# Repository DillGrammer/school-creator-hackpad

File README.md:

# Hackpad PCB — revision 1.0

Open **Hackpad.kicad_pro** in KiCad 10. The project includes its own symbol and footprint libraries; no care-package installation is needed. Original Desktop files were left unchanged.

CAD visualization, not a photograph of an assembled device.

This project was substantially generated and revised with ChatGPT/Codex assistance, following the owner's feature/layout choices and design review. See Software/Feature-status.md for unfinished integrations and Submission-status.md for funding status.

## What is finished

- 86.5 × 88.5 mm, two copper layers, 1.6 mm PCB.
- Six soldered MX switches in the established 3 × 2 layout.
- Clickable EC11 at top-left; 0.91-inch OLED immediately to its right.
- Seeed Studio XIAO RP2040 at top-right, USB-C facing the top edge.
- Routed signals, front/back ground pours, four 3.2 mm mounting holes.
- ERC, DRC and schematic parity reports included. All report zero issues.
- Gerber copper, masks, silkscreens, outline, and separate plated/non-plated drill files included.

The matching case is supplied in **Case/** as STEP and STL files, with an assembly guide and geometry checks. The native Fusion `Case/Hackpad_Case.f3d` includes editable base/cover features and a positioned knob. Case revision 1.1 corrects the CAD Y direction and knob placement; use the new case files, not earlier archives. Actual firmware and desktop-helper source are included in **Software/**; this is a development build, not a hardware-tested release. See **Software/Feature-status.md** for the exact remaining integration work.

## Pin map

View from above, USB-C at the top. Key numbers describe physical positions; existing SW references are preserved.

| Control | Reference / pad | XIAO label | RP2040 GPIO | Net |
|---|---|---|---|---|
| Top-left key | SW1 / 1 | D0 | 26 | KEY1 |
| Top-middle key | SW4 / 1 | D2 | 28 | KEY2 |
| Top-right key | SW2 / 1 | D6 | 0 | KEY3 |
| Bottom-left key | SW5 / 1 | D1 | 27 | KEY4 |
| Bottom-middle key | SW7 / 1 | D3 | 29 | KEY5 |
| Bottom-right key | SW3 / 1 | D7 | 1 | KEY6 |
| Encoder rotation A | SW6 / A | D10 | 3 | ENC_A |
| Encoder rotation B | SW6 / B | D9 | 4 | ENC_B |
| Encoder press / Enter | SW6 / S1 | D8 | 2 | ENC_CLICK |
| OLED data | J1 / 4 | D4 / SDA | 6 | OLED_SDA |
| OLED clock | J1 / 3 | D5 / SCL | 7 | OLED_SCL |
| OLED power | J1 / 2 | 3V3 | — | +3V3 |
| OLED ground | J1 / 1 | GND | — | GND |

All key pad 2 connections, encoder C, and encoder S2 connect to ground. Enable input pull-ups and software debounce for keys and encoder press. Use a quadrature decoder for rotation; configure its transitions-per-detent for the supplied encoder so one detent produces one menu step. Reverse direction in firmware if needed. Encoder press is independently wired and can mean Enter/select or another action by mode.

Six keys + three encoder inputs + two OLED signals use all 11 exposed GPIOs. Independent key wiring supports simultaneous presses without a switch matrix or diodes. Extra kit LEDs are not fitted in this design.

## Parts used from the published kit

| Quantity | Part |
|---:|---|
| 1 | Standard Seeed Studio XIAO RP2040, not RP2040 Plus |
| 6 | MX-style through-hole switches |
| 6 | 1u DSA keycaps |
| 1 | EC11 clickable rotary encoder |
| 1 | 0.91-inch 128 × 32 I²C OLED, GND–VCC–SCL–SDA |
| 1 | 4-pin 2.54 mm header supplied with/for OLED |
| 4 | M3 × 16 mm case screws, for planned enclosure |
| 4 | M3 heat-set inserts, for planned enclosure |

## Assembly assumptions

- The supplied encoder matches the Hackpad-style EC11 footprint: A/C/B terminals at 2.5 mm pitch, click terminals opposite, and two slotted metal anchors. Nominal shaft height is 20 mm. A knob is not listed in the published kit; a printable knob can be matched to the supplied shaft during case completion.
- OLED is mounted display-up and extends rightward from J1. **J1 pins run top-to-bottom: GND, 3V3, SCL, SDA.** The module envelope is assumed to be 38 × 12 mm; it is shown in the project footprint and drawing layer. Confirm the actual supplied module uses that header orientation before soldering.
- OLED is powered from 3.3 V. The common module includes I²C pull-ups; confirm that the supplied module has pull-ups to 3.3 V. Do not connect I²C pull-ups to 5 V. The MCU's weak internal pull-ups alone are not the design basis for a reliable I²C bus.
- XIAO uses the existing care-package hybrid footprint, with corrected RP2040 schematic pin names. Direct solder mounting is assumed for the planned case; tall sockets change the case fit.
- USB supplies the XIAO directly. Its 5 V breakout is deliberately unused. The circuit has no battery input.
- Switches are soldered, not hot-swap. The upper row was aligned to a common centre line; the original column spacing and lower row were preserved.
- EC11 switch anchor pads are mechanical only. They do not substitute for the C/S2 ground connections.

## Mechanical coordinates

Millimetres from PCB top-left; X right, Y down.

| Item | X | Y |
|---|---:|---:|
| Key column centres | 15.50 / 43.25 / 71.00 | — |
| Key row centres | — | 43.50 / 76.00 |
| Encoder shaft centre | 15.75 | 16.00 |
| OLED GND header pin | 27.50 | 12.19 |
| XIAO footprint centre | 75.50 | 10.50 |
| Mount H1 | 4.50 | 4.50 |
| Mount H2 | 82.00 | 29.50 |
| Mount H3 | 4.50 | 84.00 |
| Mount H4 | 82.00 | 84.00 |

The matching case uses a rounded base and removable stepped cover, four M3 screws and heat-set inserts. See **Case/Assembly-guide.md** for the assembly order, printing orientation and component fit assumptions.

## Manufacturing files

Use the Gerbers ZIP, including both drill files, for the PCB only. Board specification: two layers, FR-4, 1.6 mm thickness; design uses 0.25 mm traces, 0.20 mm minimum clearance, 0.60/0.30 mm vias, and 0.50 mm minimum copper-to-edge clearance. The Stardance design project has been created; no funding application or manufacturing order has been submitted. See Submission-status.md.

The checks validate the CAD files; this design has not been physically assembled or tested. The case has CAD checks but no physical print test; software has automated logic/display tests but still requires hardware and app integration testing.

## Sources

- [Hackpad / Stardance](https://hackpad.hackclub.com/)
- [Hack Club published kit contents](https://blueprint.hackclub.com/hackpad/parts)
- [Hackpad component guidance](https://hackpad.hackclub.com/add-components)
- [Seeed XIAO RP2040 pin map](https://wiki.seeedstudio.com/XIAO-RP2040/)

Footprints are derived from KiCad's installed libraries and the user's existing Hackpad care package. The XIAO's fabrication graphics were retained, and its courtyard added. The OLED header footprint was expanded to describe the full module envelope.

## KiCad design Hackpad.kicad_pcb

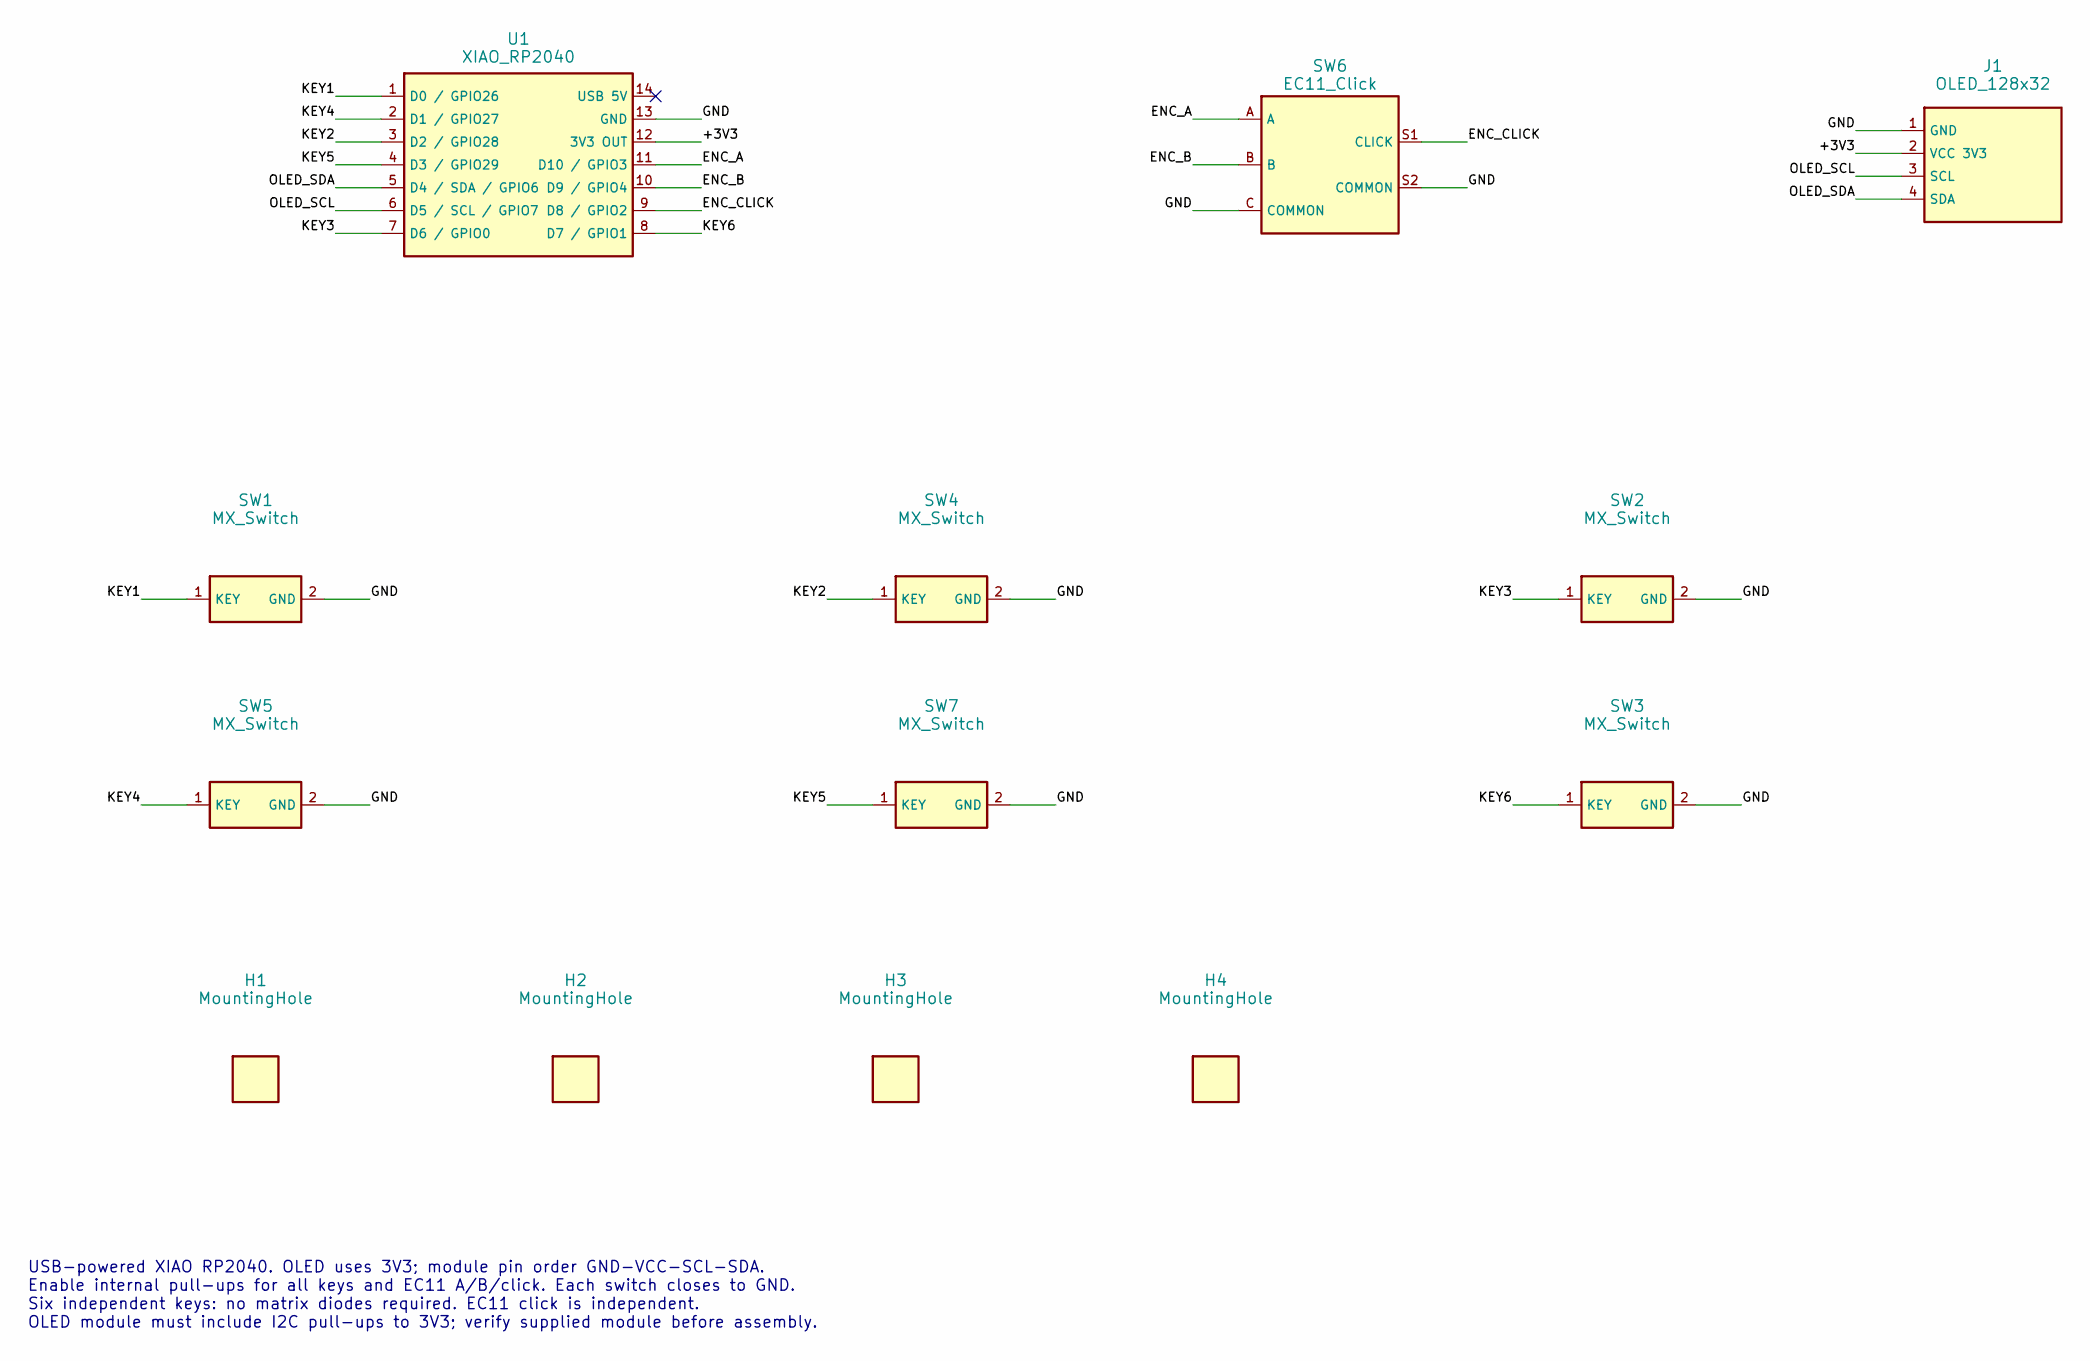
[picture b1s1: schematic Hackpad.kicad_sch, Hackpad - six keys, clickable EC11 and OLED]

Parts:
H1, H2, H3, H4: MountingHole; MountingHole_3.2mm_M3
J1: OLED_128x32; OLED_091_GND_VCC_SCL_SDA
SW1, SW2, SW3, SW4, SW5, SW7: MX_Switch; SW_Cherry_MX_1.00u_PCB
SW6: EC11_Click; RotaryEncoder_Alps_EC11E-Switch_Vertical_H20mm
U1: XIAO_RP2040; XIAO-Generic-Hybrid-14P-2.54-21X17.8MM

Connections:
/+3V3: J1.2 (VCC 3V3), U1.12 (3V3 OUT)
/ENC_A: SW6.A, U1.11 (D10 / GPIO3)
/ENC_B: SW6.B, U1.10 (D9 / GPIO4)
/ENC_CLICK: SW6.S1 (CLICK), U1.9 (D8 / GPIO2)
/GND: J1.1 (GND), SW1.2 (GND), SW2.2 (GND), SW3.2 (GND), SW4.2 (GND), SW5.2 (GND), SW6.C (COMMON), SW6.S2 (COMMON), SW7.2 (GND), U1.13 (GND)
/KEY1: SW1.1 (KEY), U1.1 (D0 / GPIO26)
/KEY2: SW4.1 (KEY), U1.3 (D2 / GPIO28)
/KEY3: SW2.1 (KEY), U1.7 (D6 / GPIO0)
/KEY4: SW5.1 (KEY), U1.2 (D1 / GPIO27)
/KEY5: SW7.1 (KEY), U1.4 (D3 / GPIO29)
/KEY6: SW3.1 (KEY), U1.8 (D7 / GPIO1)
/OLED_SCL: J1.3 (SCL), U1.6 (D5 / SCL / GPIO7)
/OLED_SDA: J1.4 (SDA), U1.5 (D4 / SDA / GPIO6)

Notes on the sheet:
USB-powered XIAO RP2040. OLED uses 3V3; module pin order GND-VCC-SCL-SDA. Enable internal pull-ups for all keys and EC11 A/B/click. Each switch closes to GND. Six independent keys: no matrix diodes required. EC11 click is independent. OLED module must include I2C pull-ups to 3V3; verify supplied mo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

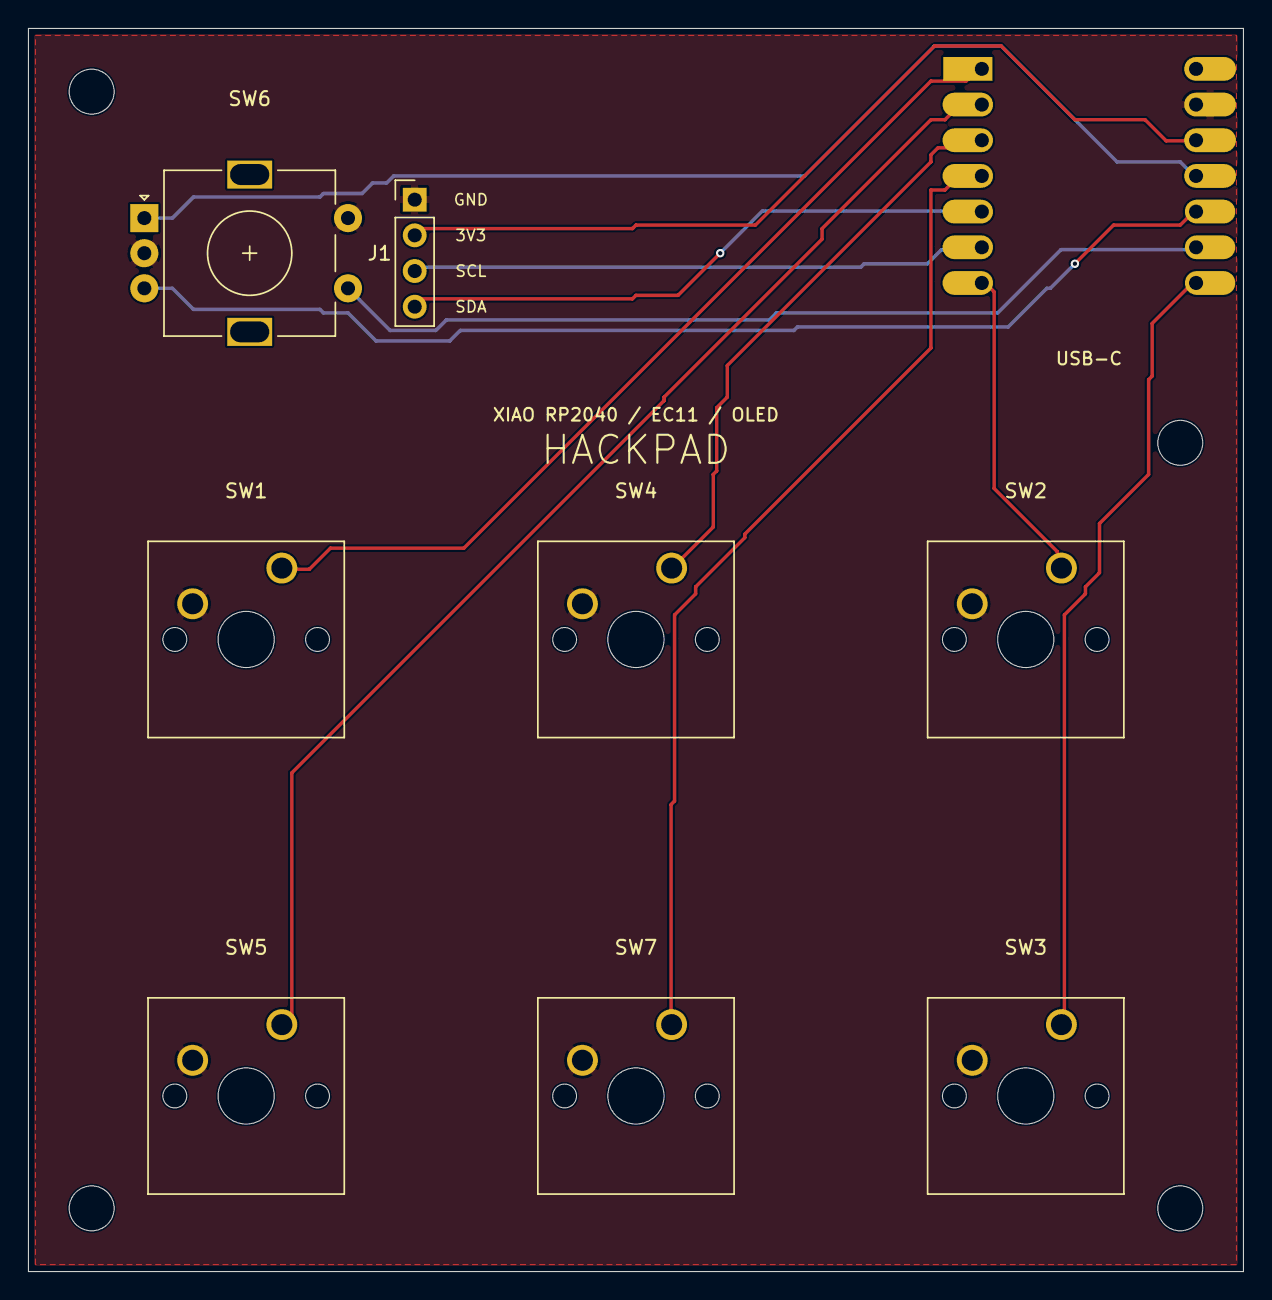
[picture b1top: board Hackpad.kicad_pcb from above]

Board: 2 copper layers, 86.5 x 88.5 mm, 13 parts (0 on the bottom side), 13 nets.
